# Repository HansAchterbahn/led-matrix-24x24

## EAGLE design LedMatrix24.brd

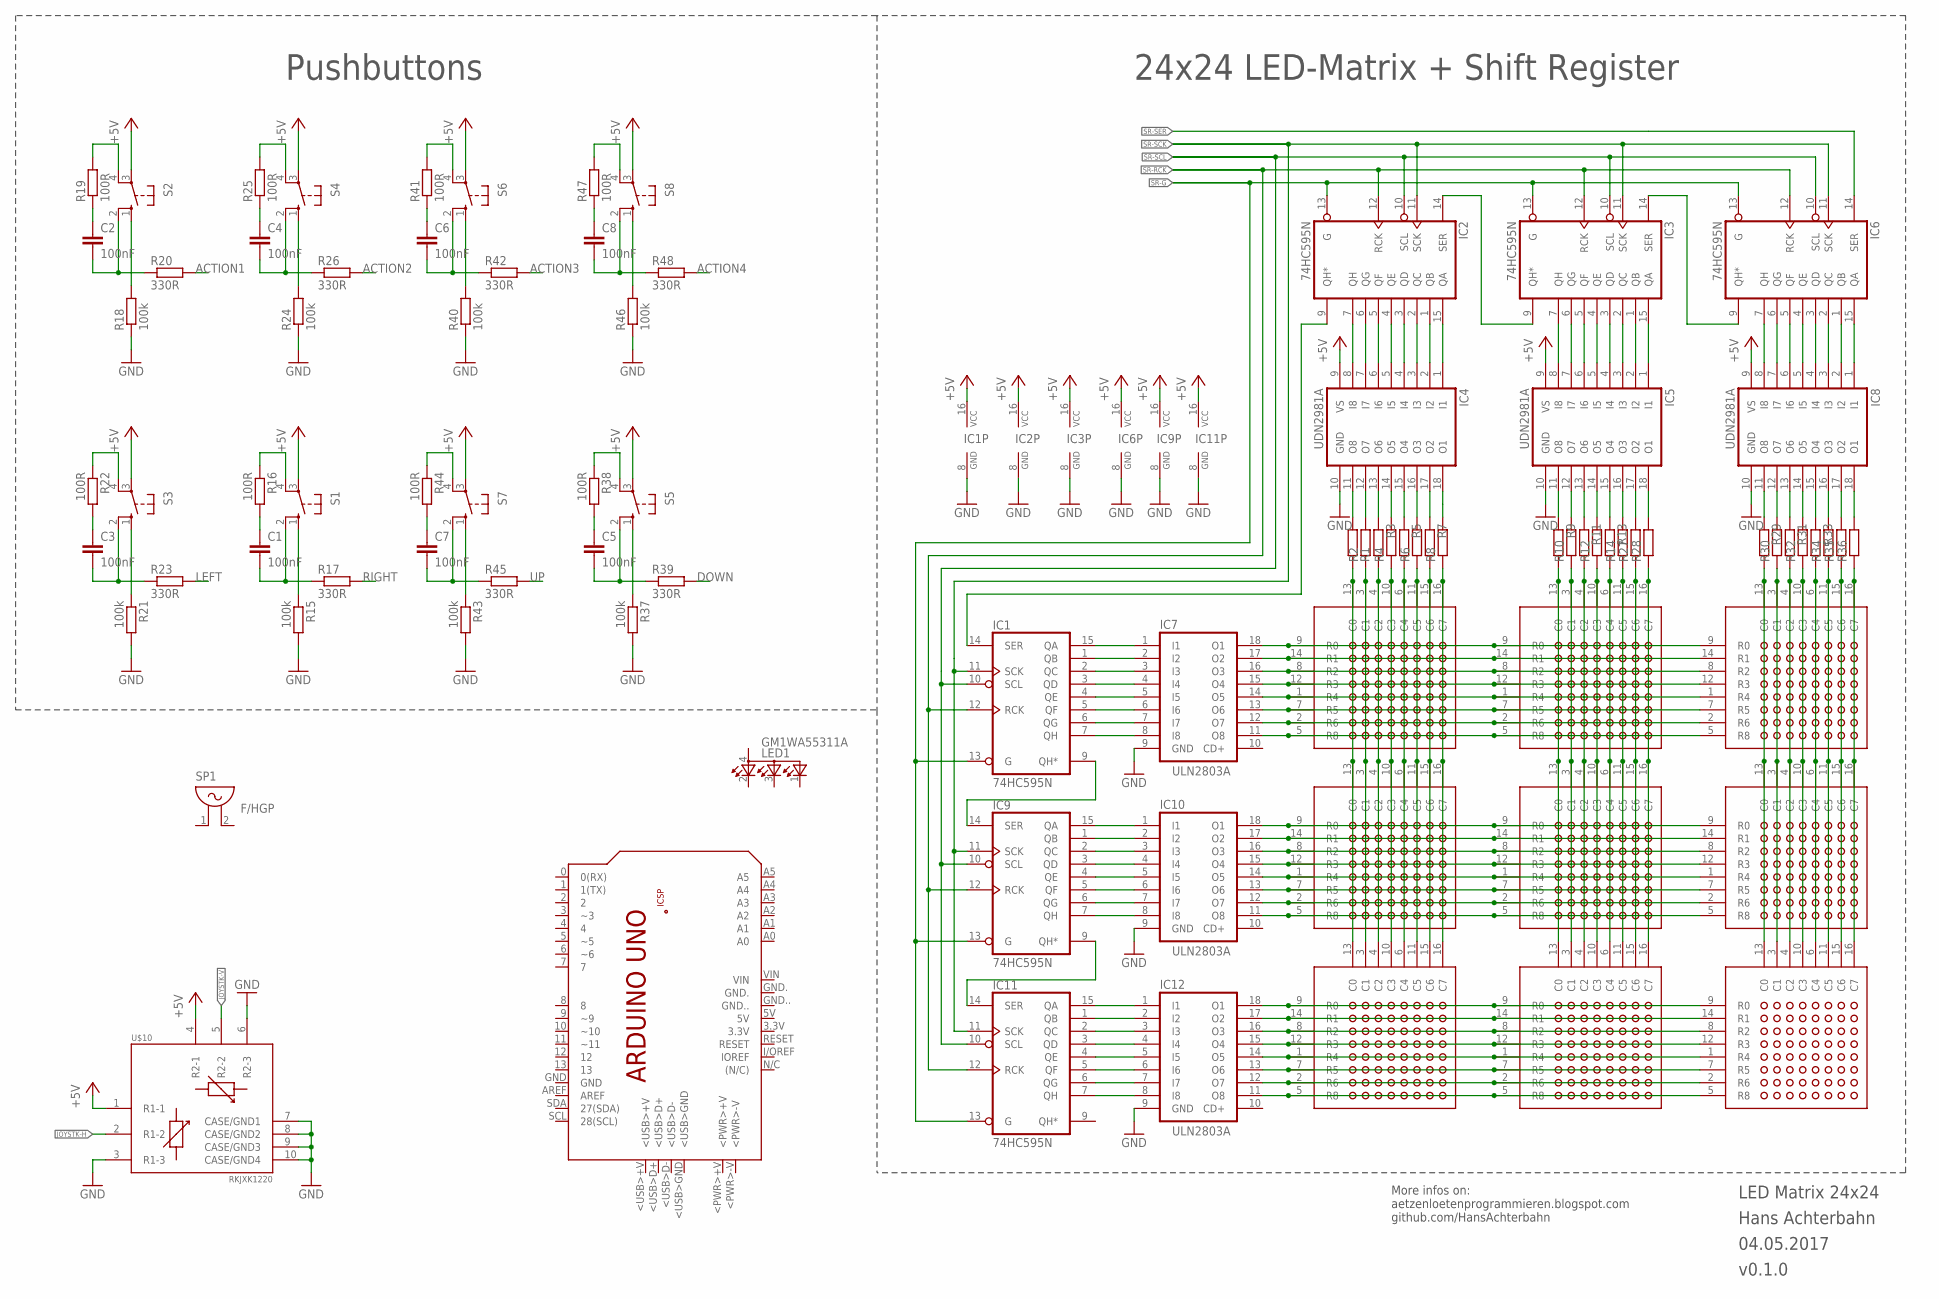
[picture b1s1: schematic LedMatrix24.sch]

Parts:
C1, C2, C3, C4, C5, C6, C7, C8: 100nF; C0805
IC1, IC2, IC3, IC6, IC9, IC11: 74HC595N; DIL16
IC4, IC5, IC8: UDN2981A; DIL18
IC7, IC10, IC12: ULN2803A; DIL18
LED1: GM1WA55311A
PCB1: ARDUINO_UNO
R1, R2, R3, R4, R5, R6, R7, R8, R9, R10, R11, R12, R13, R14, R27, R28, R29, R30, R31, R32, R33, R34, R35, R36: R-EU_0207/10; 0207/10
R15, R18, R21, R24, R37, R40, R43, R46: 100k; R0603
R16, R19, R22, R25, R38, R41, R44, R47: 100R; R0603
R17, R20, R23, R26, R39, R42, R45, R48: 330R; R0603
S1, S2, S3, S4, S5, S6, S7, S8: 10-XX; B3F-10XX
SP1: F/HGP
U$1, U$2, U$3, U$4, U$5, U$6, U$7, U$8, U$9: TOP-CA-788BS
U$10: RKJXK1220

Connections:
+5V: IC1.16 (VCC), IC2.16 (VCC), IC3.16 (VCC), IC4.9 (VS), IC5.9 (VS), IC6.16 (VCC), IC8.9 (VS), IC9.16 (VCC), IC11.16 (VCC), S1.3, S2.3, S3.3, S4.3, S5.3, S6.3, S7.3, S8.3, U$10.1 (R1-1), U$10.4 (R2-1)
ACTION1: R20.2
ACTION2: R26.2
ACTION3: R42.2
ACTION4: R48.2
DOWN: R39.2
GND: IC1.8 (GND), IC2.8 (GND), IC3.8 (GND), IC4.10 (GND), IC5.10 (GND), IC6.8 (GND), IC7.9 (GND), IC8.10 (GND), IC9.8 (GND), IC10.9 (GND), IC11.8 (GND), IC12.9 (GND), R15.2, R18.1, R21.2, R24.1, R37.2, R40.1, R43.2, R46.1, U$10.3 (R1-3), U$10.6 (R2-3), U$10.7 (CASE/GND1), U$10.8 (CASE/GND2), U$10.9 (CASE/GND3), U$10.10 (CASE/GND4)
JOYSTK-H: U$10.2 (R1-2)
JOYSTK-V: U$10.5 (R2-2)
LEFT: R23.2
unnamed: IC7.16 (O3), U$1.8 (R2), U$2.8 (R2), U$3.8 (R2)
unnamed: IC7.14 (O5), U$1.1 (R4), U$2.1 (R4), U$3.1 (R4)
unnamed: IC7.11 (O8), U$1.5 (R8), U$2.5 (R8), U$3.5 (R8)
unnamed: IC7.15 (O4), U$1.12 (R3), U$2.12 (R3), U$3.12 (R3)
unnamed: IC5.17 (O2), R27.2
unnamed: IC5.18 (O1), R28.2
unnamed: IC3.1 (QB), IC5.2 (I2)
unnamed: IC3.15 (QA), IC5.1 (I1)
unnamed: IC8.11 (O8), R29.1
unnamed: IC8.12 (O7), R30.2
unnamed: IC8.13 (O6), R31.1
unnamed: IC8.14 (O5), R32.2
unnamed: IC8.15 (O4), R33.1
unnamed: IC8.16 (O3), R34.2
unnamed: IC6.2 (QC), IC8.3 (I3)
unnamed: IC6.3 (QD), IC8.4 (I4)
unnamed: IC7.13 (O6), U$1.7 (R5), U$2.7 (R5), U$3.7 (R5)
unnamed: IC7.12 (O7), U$1.2 (R6), U$2.2 (R6), U$3.2 (R6)
unnamed: IC6.4 (QE), IC8.5 (I5)
unnamed: IC4.11 (O8), R1.2
unnamed: IC4.12 (O7), R2.2
unnamed: IC4.13 (O6), R3.1
unnamed: IC4.14 (O5), R4.2
unnamed: IC4.15 (O4), R5.1
unnamed: IC4.16 (O3), R6.2
unnamed: IC4.17 (O2), R7.1
unnamed: IC4.18 (O1), R8.2
unnamed: IC5.11 (O8), R9.1
unnamed: IC5.12 (O7), R10.2
unnamed: IC5.13 (O6), R11.1
unnamed: IC5.14 (O5), R12.2
unnamed: IC5.15 (O4), R13.1
unnamed: IC5.16 (O3), R14.2
unnamed: IC2.1 (QB), IC4.2 (I2)
unnamed: IC2.2 (QC), IC4.3 (I3)
unnamed: IC2.3 (QD), IC4.4 (I4)
unnamed: IC2.4 (QE), IC4.5 (I5)
unnamed: IC2.5 (QF), IC4.6 (I6)
unnamed: IC2.6 (QG), IC4.7 (I7)
unnamed: IC2.7 (QH), IC4.8 (I8)
unnamed: IC2.15 (QA), IC4.1 (I1)
unnamed: R22.1, S3.4 (P1)
unnamed: IC3.2 (QC), IC5.3 (I3)
unnamed: IC3.3 (QD), IC5.4 (I4)
unnamed: IC3.4 (QE), IC5.5 (I5)
unnamed: IC3.5 (QF), IC5.6 (I6)
unnamed: IC3.6 (QG), IC5.7 (I7)
unnamed: IC3.7 (QH), IC5.8 (I8)
unnamed: C1.1, R16.2
unnamed: IC2.14 (SER), IC3.9 (QH*)
unnamed: IC1.14 (SER), IC2.9 (QH*)
unnamed: R1.1, R2.1, U$1.3 (C1), U$1.13 (C0), U$4.3 (C1), U$4.13 (C0), U$7.3 (C1), U$7.13 (C0)
unnamed: R3.2, U$1.4 (C2), U$4.4 (C2), U$7.4 (C2)
unnamed: R4.1, U$1.10 (C3), U$4.10 (C3), U$7.10 (C3)
unnamed: R5.2, U$1.6 (C4), U$4.6 (C4), U$7.6 (C4)
unnamed: R18.2, S2.1 (S)
unnamed: R19.2, S2.4 (P1)
unnamed: C1.2, R17.1, S1.2 (S1)
unnamed: R16.1, S1.4 (P1)
unnamed: C3.2, R23.1, S3.2 (S1)
unnamed: C2.2, R20.1, S2.2 (S1)
unnamed: R21.1, S3.1 (S)
unnamed: R15.1, S1.1 (S)
unnamed: C4.1, R25.1
unnamed: R25.2, S4.4 (P1)
unnamed: C2.1, R19.1
unnamed: C4.2, R26.1, S4.2 (S1)
unnamed: C3.1, R22.2
unnamed: R24.2, S4.1 (S)
unnamed: IC6.5 (QF), IC8.6 (I6)
unnamed: IC6.6 (QG), IC8.7 (I7)
unnamed: IC1.2 (QC), IC7.3 (I3)
unnamed: IC1.3 (QD), IC7.4 (I4)
unnamed: IC1.4 (QE), IC7.5 (I5)
unnamed: IC1.5 (QF), IC7.6 (I6)
unnamed: IC1.6 (QG), IC7.7 (I7)
unnamed: IC1.7 (QH), IC7.8 (I8)
unnamed: IC6.7 (QH), IC8.8 (I8)
unnamed: IC3.14 (SER), IC6.9 (QH*)
unnamed: C5.1, R38.2
unnamed: C6.1, R41.1
unnamed: C7.1, R44.2
unnamed: R6.1, U$1.11 (C5), U$4.11 (C5), U$7.11 (C5)
unnamed: IC8.17 (O2), R35.2
unnamed: IC8.18 (O1), R36.2
unnamed: IC6.1 (QB), IC8.2 (I2)
unnamed: IC6.15 (QA), IC8.1 (I1)
unnamed: R7.2, U$1.15 (C6), U$4.15 (C6), U$7.15 (C6)
unnamed: R8.1, U$1.16 (C7), U$4.16 (C7), U$7.16 (C7)
unnamed: R9.2, U$2.13 (C0), U$5.13 (C0), U$8.13 (C0)
unnamed: R10.1, U$2.3 (C1), U$5.3 (C1), U$8.3 (C1)
unnamed: R11.2, U$2.4 (C2), U$5.4 (C2), U$8.4 (C2)
unnamed: R12.1, U$2.10 (C3), U$5.10 (C3), U$8.10 (C3)
unnamed: R13.2, U$2.6 (C4), U$5.6 (C4), U$8.6 (C4)
unnamed: R14.1, U$2.11 (C5), U$5.11 (C5), U$8.11 (C5)
unnamed: IC1.9 (QH*), IC9.14 (SER)
unnamed: IC9.9 (QH*), IC11.14 (SER)
unnamed: R29.2, U$3.13 (C0), U$6.13 (C0), U$9.13 (C0)
unnamed: R30.1, U$3.3 (C1), U$6.3 (C1), U$9.3 (C1)
unnamed: R31.2, U$3.4 (C2), U$6.4 (C2), U$9.4 (C2)
unnamed: R32.1, U$3.10 (C3), U$6.10 (C3), U$9.10 (C3)
unnamed: R33.2, U$3.6 (C4), U$6.6 (C4), U$9.6 (C4)
unnamed: R34.1, U$3.11 (C5), U$6.11 (C5), U$9.11 (C5)
unnamed: R35.1, U$3.15 (C6), U$6.15 (C6), U$9.15 (C6)
unnamed: R36.1, U$3.16 (C7), U$6.16 (C7), U$9.16 (C7)
unnamed: R28.1, U$2.16 (C7), U$5.16 (C7), U$8.16 (C7)
unnamed: R27.1, U$2.15 (C6), U$5.15 (C6), U$8.15 (C6)
unnamed: IC7.17 (O2), U$1.14 (R1), U$2.14 (R1), U$3.14 (R1)
unnamed: IC7.18 (O1), U$1.9 (R0), U$2.9 (R0), U$3.9 (R0)
unnamed: IC10.13 (O6), U$4.7 (R5), U$5.7 (R5), U$6.7 (R5)
unnamed: IC10.12 (O7), U$4.2 (R6), U$5.2 (R6), U$6.2 (R6)
unnamed: IC1.15 (QA), IC7.1 (I1)
unnamed: IC9.2 (QC), IC10.3 (I3)
unnamed: IC9.3 (QD), IC10.4 (I4)
unnamed: IC9.4 (QE), IC10.5 (I5)
unnamed: IC9.5 (QF), IC10.6 (I6)
unnamed: IC9.6 (QG), IC10.7 (I7)
unnamed: IC9.7 (QH), IC10.8 (I8)
unnamed: IC10.16 (O3), U$4.8 (R2), U$5.8 (R2), U$6.8 (R2)
unnamed: IC10.14 (O5), U$4.1 (R4), U$5.1 (R4), U$6.1 (R4)
unnamed: IC10.11 (O8), U$4.5 (R8), U$5.5 (R8), U$6.5 (R8)
unnamed: IC10.15 (O4), U$4.12 (R3), U$5.12 (R3), U$6.12 (R3)
unnamed: R44.1, S7.4 (P1)
unnamed: R41.2, S6.4 (P1)
unnamed: R38.1, S5.4 (P1)
unnamed: IC10.17 (O2), U$4.14 (R1), U$5.14 (R1), U$6.14 (R1)
unnamed: IC10.18 (O1), U$4.9 (R0), U$5.9 (R0), U$6.9 (R0)
unnamed: IC12.13 (O6), U$7.7 (R5), U$8.7 (R5), U$9.7 (R5)
unnamed: IC12.12 (O7), U$7.2 (R6), U$8.2 (R6), U$9.2 (R6)
unnamed: IC1.1 (QB), IC7.2 (I2)
unnamed: IC11.2 (QC), IC12.3 (I3)
unnamed: IC11.3 (QD), IC12.4 (I4)
unnamed: IC11.4 (QE), IC12.5 (I5)
unnamed: IC11.5 (QF), IC12.6 (I6)
unnamed: IC11.6 (QG), IC12.7 (I7)
unnamed: IC11.7 (QH), IC12.8 (I8)
unnamed: IC12.16 (O3), U$7.8 (R2), U$8.8 (R2), U$9.8 (R2)
unnamed: IC12.14 (O5), U$7.1 (R4), U$8.1 (R4), U$9.1 (R4)
unnamed: IC12.11 (O8), U$7.5 (R8), U$8.5 (R8), U$9.5 (R8)
unnamed: IC12.15 (O4), U$7.12 (R3), U$8.12 (R3), U$9.12 (R3)
unnamed: C5.2, R39.1, S5.2 (S1)
unnamed: C7.2, R45.1, S7.2 (S1)
unnamed: IC12.17 (O2), U$7.14 (R1), U$8.14 (R1), U$9.14 (R1)
unnamed: IC12.18 (O1), U$7.9 (R0), U$8.9 (R0), U$9.9 (R0)
unnamed: IC9.15 (QA), IC10.1 (I1)
unnamed: IC9.1 (QB), IC10.2 (I2)
unnamed: IC11.15 (QA), IC12.1 (I1)
unnamed: IC11.1 (QB), IC12.2 (I2)
unnamed: C6.2, R42.1, S6.2 (S1)
unnamed: R40.2, S6.1 (S)
unnamed: R43.1, S7.1 (S)
unnamed: R37.1, S5.1 (S)
unnamed: C8.1, R47.1
unnamed: R47.2, S8.4 (P1)
unnamed: C8.2, R48.1, S8.2 (S1)
unnamed: R46.2, S8.1 (S)
RIGHT: R17.2
SR-G: IC1.13 (G), IC2.13 (G), IC3.13 (G), IC6.13 (G), IC9.13 (G), IC11.13 (G)
SR-RCK: IC1.12 (RCK), IC2.12 (RCK), IC3.12 (RCK), IC6.12 (RCK), IC9.12 (RCK), IC11.12 (RCK)
SR-SCK: IC1.11 (SCK), IC2.11 (SCK), IC3.11 (SCK), IC6.11 (SCK), IC9.11 (SCK), IC11.11 (SCK)
SR-SCL: IC1.10 (SCL), IC2.10 (SCL), IC3.10 (SCL), IC6.10 (SCL), IC9.10 (SCL), IC11.10 (SCL)
SR-SER: IC6.14 (SER)
UP: R45.2

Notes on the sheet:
ULN2803A
LED Matrix 24x24
Hans Achterbahn
04.05.2017
v0.1.0
More infos on: aetzenloetenprogrammieren.blogspot.com github.com/HansAchterbahn
24x24 LED-Matrix + Shift Register
Pushbuttons

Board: 2 copper layers, 89 parts (19 on the bottom side), 162 nets, no tracks yet.

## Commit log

2017-05-04 New Projekt: LED matrix with 24x24 LEDs, D-Pad, joystick, action buttons and Arduino interface
2017-05-23 LED Matrizen an Raster 2.5mm angepasst und Buzzer eingefügt
